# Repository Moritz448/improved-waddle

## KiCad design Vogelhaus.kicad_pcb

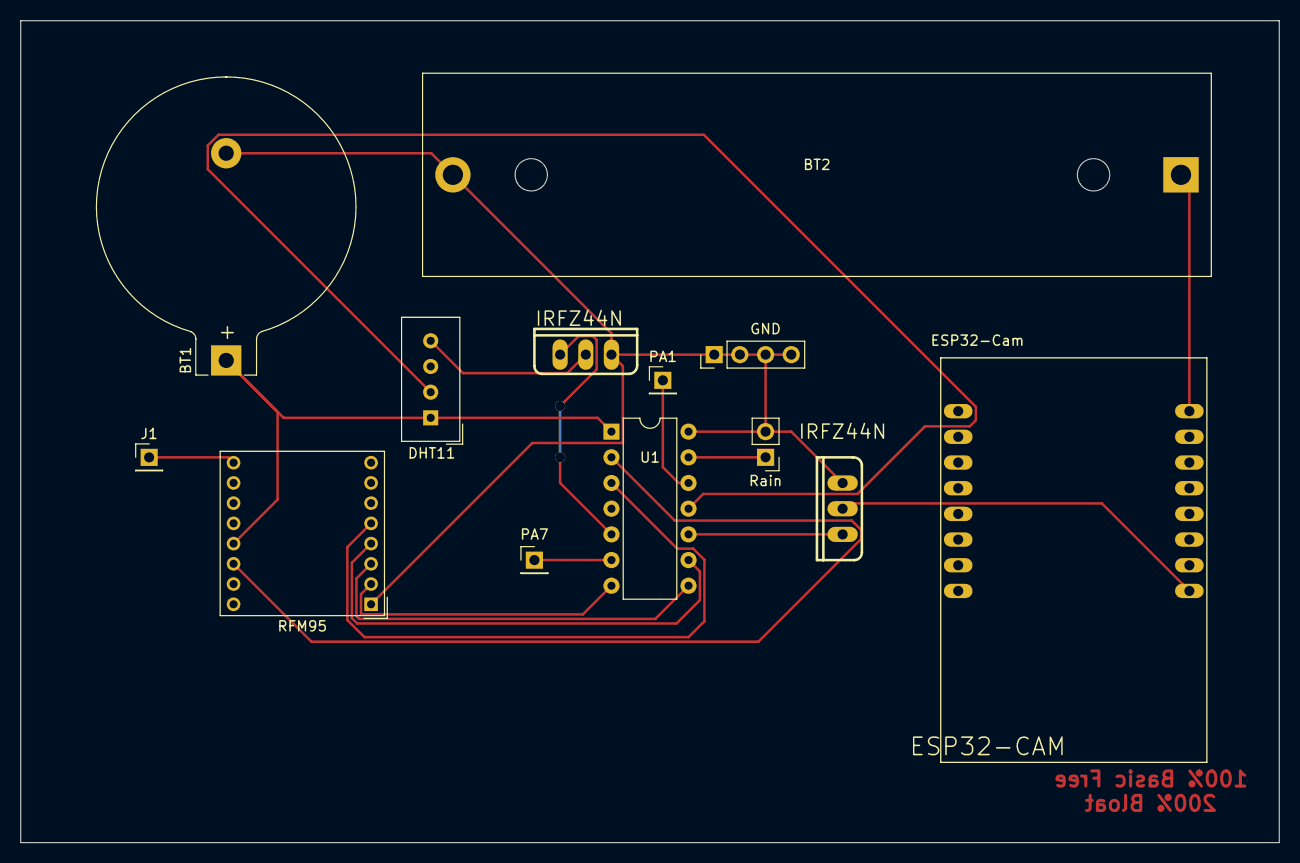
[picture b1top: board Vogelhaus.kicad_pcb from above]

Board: 2 copper layers, 124.5 x 81.3 mm, 13 parts (0 on the bottom side), 17 nets.

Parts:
BT1: Coin_Battery; BatteryHolder_Keystone_104_1x23mm
BT2: 18650_Battery; BatteryHolder_MPD_BH-18650-PC2
DHT11: DHT11; Aosong_DHT11_5.5x12.0_P2.54mm
ESP32-Cam: ESP32-CAM
GND: Ground; PinHeader_1x04_P2.54mm_Vertical
IRFZ44N, IRFZ44N#2: IRFZ44N; TO-220
J1: Antenna; PinHeader_1x01_P2.54mm_Vertical
PA1: PA1; PinHeader_1x01_P2.54mm_Vertical
PA7: PA7; PinHeader_1x01_P2.54mm_Vertical
RFM95: RFM95W-868S2; HOPERF_RFM9XW_THT
Rain: Rain Sensor; PinHeader_1x02_P2.54mm_Vertical
U1: ATtiny84V-10P; DIP-14_W7.62mm

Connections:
GND: BT1.2 (-), BT2.2 (-), GND.1, GND.2, GND.3, GND.4, IRFZ44N.3, IRFZ44N#2.3, RFM95.1 (GND), Rain.2, U1.14 (GND)
unnamed: BT1.1 (+), DHT11.1 (VCC), RFM95.13 (3.3V), U1.1 (VCC)
unnamed: BT2.1 (+), ESP32-Cam.P$16 (3V3)
unnamed: ESP32-Cam.P$9 (.GND), IRFZ44N#2.2
unnamed: J1.1, RFM95.9 (ANT)
unnamed: Rain.1, U1.13 (AREF/PA0)
unnamed: PA1.1, U1.12 (PA1)
unnamed: PA7.1, U1.6 (PA7)
unnamed: DHT11.2 (IO), U1.11 (PA2)
unnamed: DHT11.4 (GND), IRFZ44N.2
unnamed: RFM95.14 (DIO0), U1.2 (XTAL1/PB0)
unnamed: RFM95.5 (NSS), U1.3 (XTAL2/PB1)
unnamed: IRFZ44N.1, U1.5 (PB2)
unnamed: RFM95.2 (MISO), U1.7 (PA6)
unnamed: RFM95.3 (MOSI), U1.8 (PA5)
unnamed: RFM95.4 (SCK), U1.9 (PA4)
unnamed: IRFZ44N#2.1, U1.10 (PA3)

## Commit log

2022-04-12 Moved files in Folder
